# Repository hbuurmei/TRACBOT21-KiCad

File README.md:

# TRACBOT-KiCad
KiCad circuits for ME210 competition Win'24.

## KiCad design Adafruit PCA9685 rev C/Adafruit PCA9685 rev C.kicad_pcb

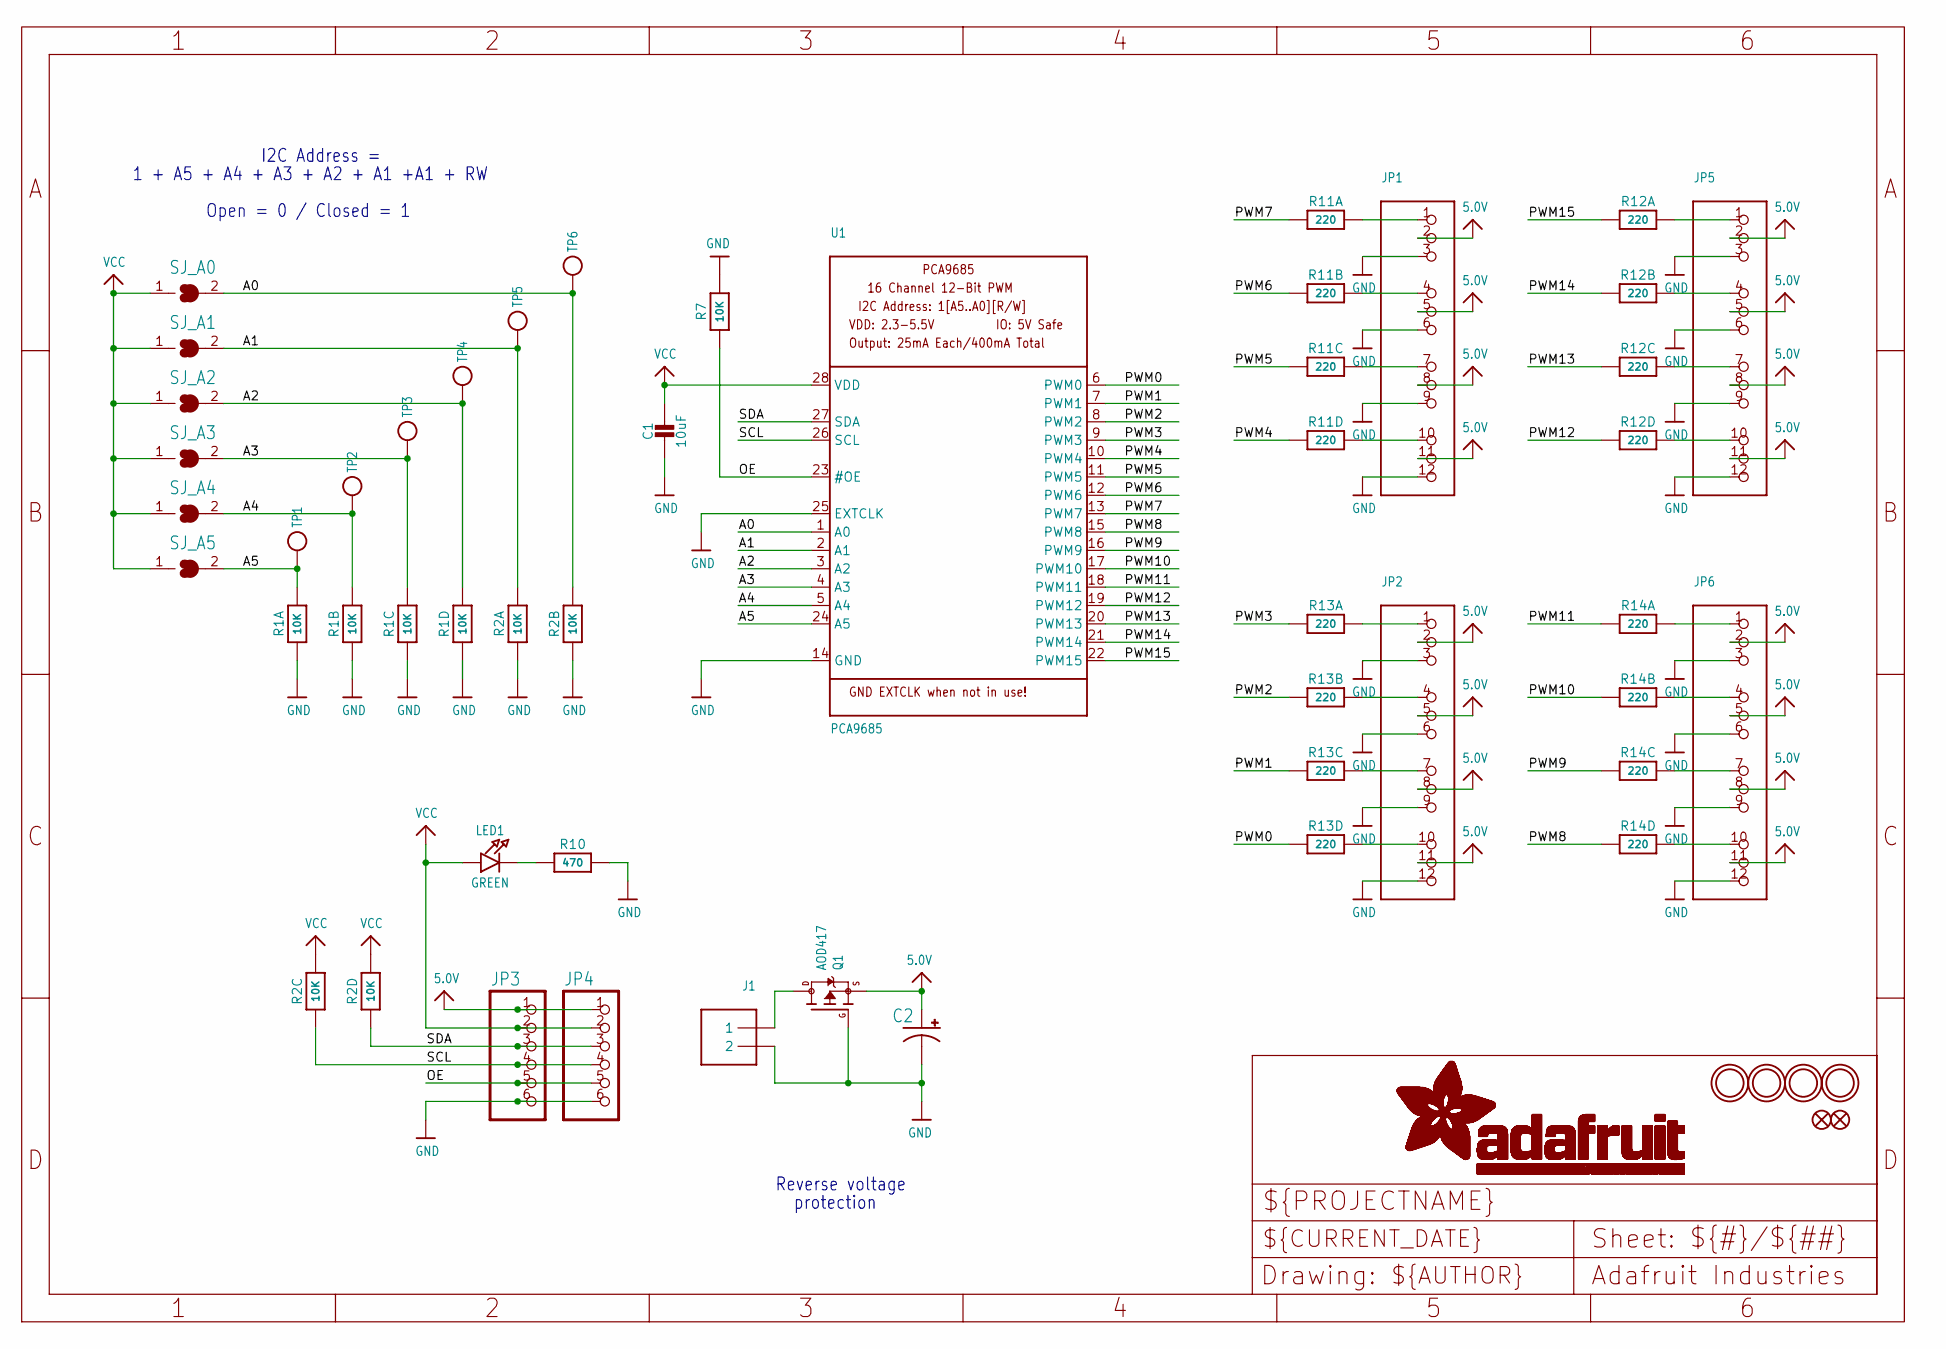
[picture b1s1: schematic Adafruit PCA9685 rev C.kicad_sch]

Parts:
C1: 10uF; 0805-NO
C2: CPOL-USE3.5-8; E3,5-8
FID1, FID2: FIDUCIAL""; FIDUCIAL_1MM
J1: TERMBLOCK_1X2; TERMBLOCK_1X2-3.5MM
JP1, JP2, JP5, JP6: HEADER-3X04; 3X04
JP3, JP4: PINHD-1X6CB; 1X06-CLEANBIG
LED1: GREEN; CHIPLED_0805_NOOUTLINE
Q1: AOD417; TO252
R1, R2: 10K; RESPACK_4X0603
R7: 10K; 0805-NO
R10: 470; _0805MP
R11, R12, R13, R14: 220; RESPACK_4X0603
SJ_A0, SJ_A1, SJ_A2, SJ_A3, SJ_A4, SJ_A5: SOLDERJUMPERREFLOW_NOPASTE; SOLDERJUMPER_REFLOW_NOPASTE
TP1, TP2, TP3, TP4, TP5, TP6: TESTPOINTROUND1MM; TESTPOINT_ROUND_1MM
U1: PCA9685; TSSOP28
U$47, U$48, U$49, U$50: MOUNTINGHOLE2.5; MOUNTINGHOLE_2.5_PLATED

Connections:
5.0V: C2.+, JP1.2, JP1.5, JP1.8, JP1.11, JP2.2, JP2.5, JP2.8, JP2.11, JP3.1, JP4.1, JP5.2, JP5.5, JP5.8, JP5.11, JP6.2, JP6.5, JP6.8, JP6.11, Q1.2 (S)
A0: R2.7 (2), SJ_A0.2, TP6.P$1, U1.1 (A0)
A1: R2.8 (2), SJ_A1.2, TP5.P$1, U1.2 (A1)
A2: R1.5 (2), SJ_A2.2, TP4.P$1, U1.3 (A2)
A3: R1.6 (2), SJ_A3.2, TP3.P$1, U1.4 (A3)
A4: R1.7 (2), SJ_A4.2, TP2.P$1, U1.5 (A4)
A5: R1.8 (2), SJ_A5.2, TP1.P$1, U1.24 (A5)
GND: C1.2, C2.-, J1.2, JP1.3, JP1.6, JP1.9, JP1.12, JP2.3, JP2.6, JP2.9, JP2.12, JP3.6, JP4.6, JP5.3, JP5.6, JP5.9, JP5.12, JP6.3, JP6.6, JP6.9, JP6.12, Q1.1 (G), R1.1, R1.2 (1), R1.3 (1), R1.4 (1), R2.1, R2.2 (1), R7.2, R10.2, U1.14 (GND), U1.25 (EXTCLK)
unnamed: LED1.C, R10.1
unnamed: JP1.4, R11.7 (2)
unnamed: JP1.1, R11.8 (2)
unnamed: JP1.7, R11.6 (2)
unnamed: JP1.10, R11.5 (2)
unnamed: JP2.1, R13.8 (2)
unnamed: JP2.4, R13.7 (2)
unnamed: JP2.7, R13.6 (2)
unnamed: JP2.10, R13.5 (2)
unnamed: JP6.10, R14.5 (2)
unnamed: JP6.7, R14.6 (2)
unnamed: JP6.4, R14.7 (2)
unnamed: JP6.1, R14.8 (2)
unnamed: JP5.10, R12.5 (2)
unnamed: JP5.7, R12.6 (2)
unnamed: JP5.4, R12.7 (2)
unnamed: JP5.1, R12.8 (2)
OE: JP3.5, JP4.5, R7.1, U1.23 (#OE)
PWM0: R13.4 (1), U1.6 (PWM0)
PWM1: R13.3 (1), U1.7 (PWM1)
PWM2: R13.2 (1), U1.8 (PWM2)
PWM3: R13.1, U1.9 (PWM3)
PWM4: R11.4 (1), U1.10 (PWM4)
PWM5: R11.3 (1), U1.11 (PWM5)
PWM6: R11.2 (1), U1.12 (PWM6)
PWM7: R11.1, U1.13 (PWM7)
PWM8: R14.4 (1), U1.15 (PWM8)
PWM9: R14.3 (1), U1.16 (PWM9)
PWM10: R14.2 (1), U1.17 (PWM10)
PWM11: R14.1, U1.18 (PWM11)
PWM12: R12.4 (1), U1.19 (PWM12)
PWM13: R12.3 (1), U1.20 (PWM13)
PWM14: R12.2 (1), U1.21 (PWM14)
PWM15: R12.1, U1.22 (PWM15)
PWRIN: J1.1, Q1.3 (D)
SCL: JP3.4, JP4.4, R2.3 (1), U1.26 (SCL)
SDA: JP3.3, JP4.3, R2.4 (1), U1.27 (SDA)
VCC: C1.1, JP3.2, JP4.2, LED1.A, R2.5 (2), R2.6 (2), SJ_A0.1, SJ_A1.1, SJ_A2.1, SJ_A3.1, SJ_A4.1, SJ_A5.1, U1.28 (VDD)

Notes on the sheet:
I2C Address =
Reverse voltage
Open = 0 / Closed = 1
1 + A5 + A4 + A3 + A2 + A1 +A1 + RW
protection

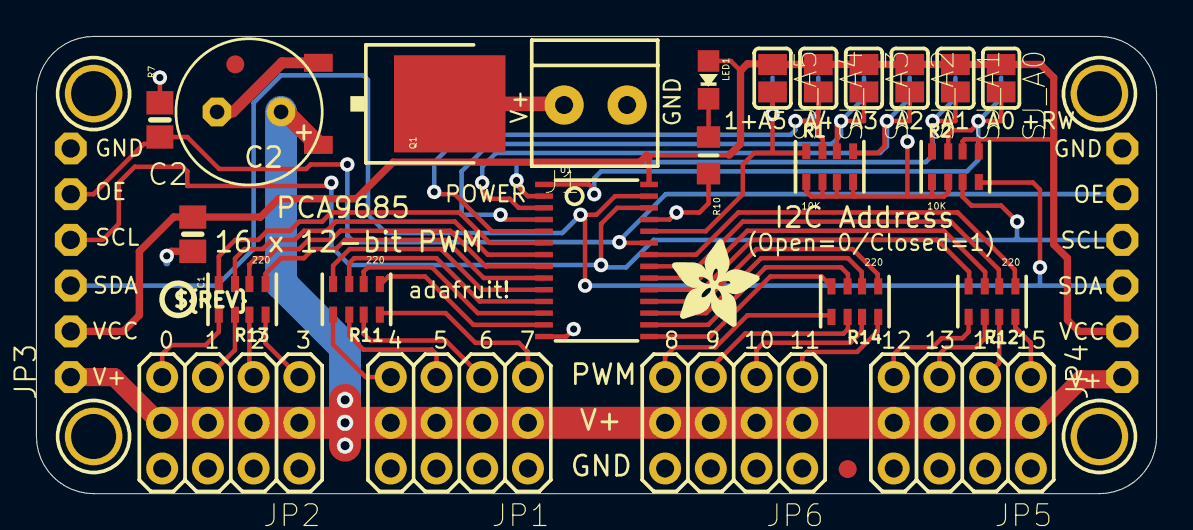
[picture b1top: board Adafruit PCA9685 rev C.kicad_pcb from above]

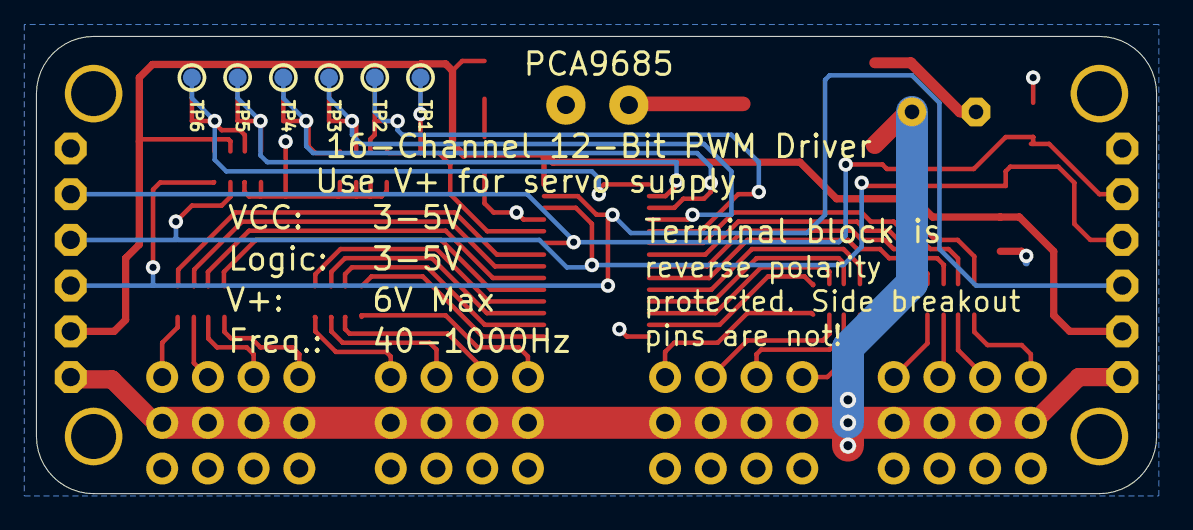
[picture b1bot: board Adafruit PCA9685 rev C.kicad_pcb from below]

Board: 2 copper layers, 62.2 x 25.4 mm, 40 parts (6 on the bottom side), 46 nets.

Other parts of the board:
U$51: ADAFRUIT_5MM
U$54: PCBFEAT-REV-040

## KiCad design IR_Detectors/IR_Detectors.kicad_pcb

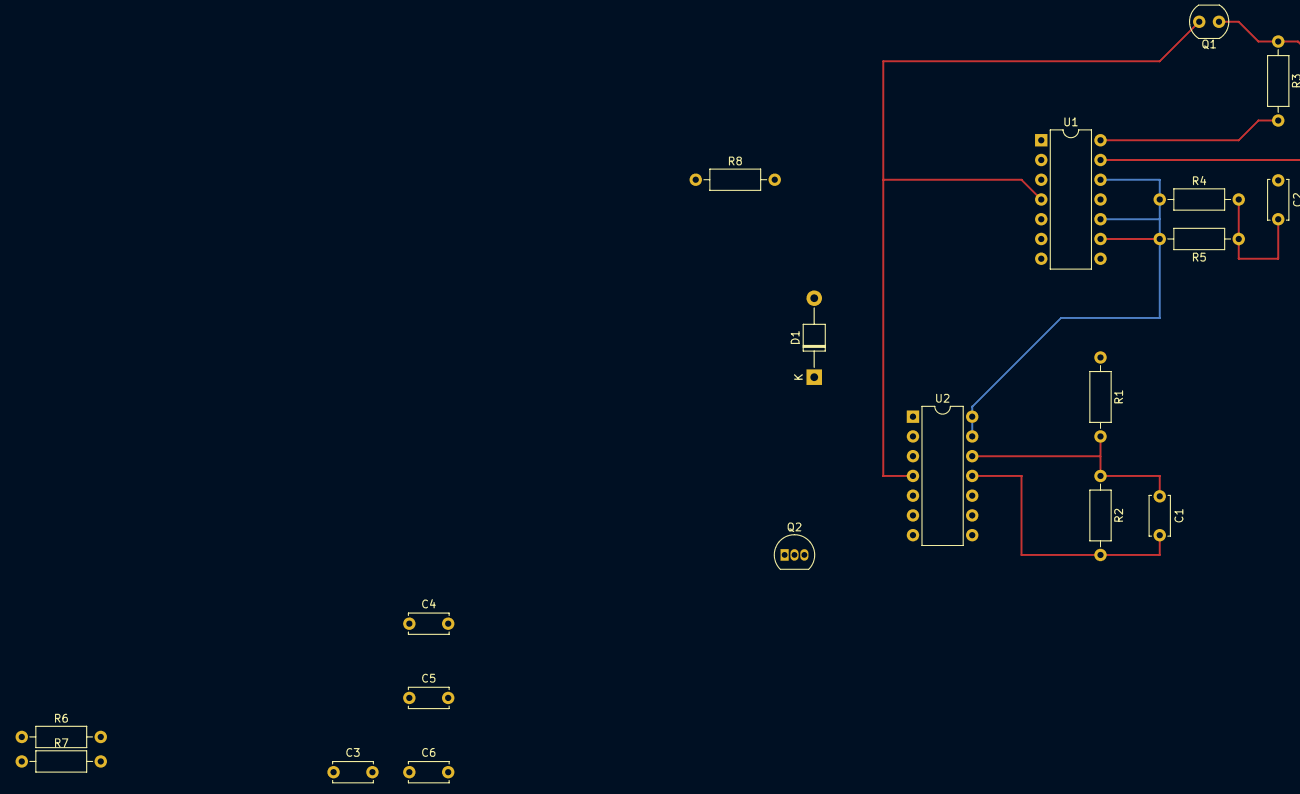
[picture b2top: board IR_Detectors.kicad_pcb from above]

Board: 2 copper layers, 19 parts (0 on the bottom side), 14 nets.

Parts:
C1, C5, C6: C; C_Disc_D5.0mm_W2.5mm_P5.00mm
C2, C3: 10nF; C_Disc_D5.0mm_W2.5mm_P5.00mm
C4: 22nF; C_Disc_D5.0mm_W2.5mm_P5.00mm
D1: D; D_T-1_P10.16mm_Horizontal
Q1: LTR-3208E; R_LDR_4.9x4.2mm_P2.54mm_Vertical
Q2: 2N7000; TO-92_Inline
R1, R2, R4, R6, R7: 10k; R_Axial_DIN0207_L6.3mm_D2.5mm_P10.16mm_Horizontal
R3: 680; R_Axial_DIN0207_L6.3mm_D2.5mm_P10.16mm_Horizontal
R5: 2.2k; R_Axial_DIN0207_L6.3mm_D2.5mm_P10.16mm_Horizontal
R8: 470; R_Axial_DIN0207_L6.3mm_D2.5mm_P10.16mm_Horizontal
U1: LM6144xIx; DIP-14_W7.62mm
U2: MCP6294; DIP-14_W7.62mm

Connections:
+5V: Q1.2 (C), R1.1, U1.4 (V+), U2.4 (V+)
/+2.5V: R4.1, R7.1, U1.10 (+), U1.12 (+), U2.13 (-), U2.14
GND: C1.2, C4.2, C6.2, Q2.1 (S), R2.2, U1.11 (V-), U2.11 (V-)
unnamed: C2.1, R3.2, U1.14
unnamed: C2.2, R4.2, R5.1
unnamed: C3.1, R6.2, U1.8
unnamed: C3.2, R7.2
unnamed: C5.2, D1.2 (A), U1.7
unnamed: C5.1, C6.1, D1.1 (K), Q2.3 (D), U1.6 (-), U2.3 (+)
unnamed: Q1.1 (E), R3.1, U1.13 (-)
unnamed: C4.1, R8.2, U1.5 (+)
unnamed: R5.2, R6.1, U1.9 (-)
unnamed: U2.1, U2.2 (-)
unnamed: C1.1, R1.2, R2.1, U2.12 (+)

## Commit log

2024-02-21 Add empty Dumper circuit
2024-02-21 add motor driver circuit
2024-02-21 Add Dumper circuit with two servos
2024-02-22 added voltage regulator
2024-02-22 clean upmotor diagram
2024-02-22 increase arduino diagram size
2024-02-22 oops
2024-02-23 +limit switches
    Added limit switches to the existing motor+driver+batteries kicad. Other sensors should be added as we get them to make a full drivetrain+sensor schematic.
2024-02-24 update voltage regulators:
2024-02-28 initial ir detector design
2024-02-29 single IR detector design
2024-03-14 Update placing diagrams
2024-03-14 ir detector schematic
2024-03-14 add i2c servo driver and imu
